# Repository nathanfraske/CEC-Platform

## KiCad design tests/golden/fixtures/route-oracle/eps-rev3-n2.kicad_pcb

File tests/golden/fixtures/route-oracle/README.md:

# route-oracle grader fixtures (SLICE-1a)

Two EPS-8pin PLACEMENTS (unrouted), used by `tests/test_route_oracle.py` to give the
route-oracle grader (`cec_synth_pipeline.route_oracle_grade`) durable PASS/FAIL teeth +
the proxy-vs-oracle disagreement case.

- `eps-rev3-n2.kicad_pcb` — the FIRST gate-clean EPS placement (commit 515cae7): the INA238
  current-sense ICs backed off the shunt 1.4 mm so the §6.8 inner-edge Kelvin tap clears the
  IC's own GND/+3V3 pads. Routes GATE-CLEAN under the recipe (kelvin_ok, foreign 0/0, drc 0,
  thermal ~62 C). The grader must rank it PASS.
- `eps-rev3-widegap-m.kicad_pcb` — its PRE-FIX parent (INA seated hard against the shunt).
  PROXY-BETTER (slightly lower HPWL, the tighter seat = shorter wires) but routes DIRTY
  (kelvin_ok=False: the LO->IN- tap strands). The grader must rank it FAIL. This is the
  concrete placement_proxy-vs-oracle DISAGREEMENT: the proxy prefers the tighter (broken)
  parent; the oracle, by actually routing, correctly demotes it.

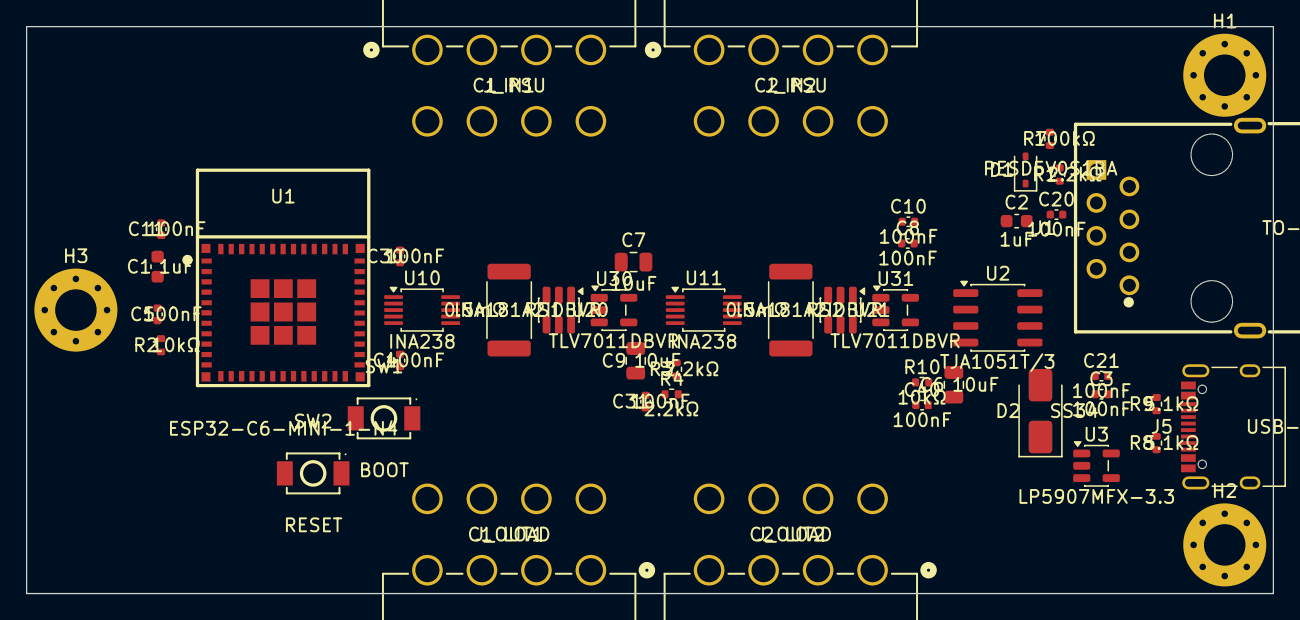
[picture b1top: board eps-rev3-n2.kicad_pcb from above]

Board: 4 copper layers, 96.1 x 43.7 mm, 48 parts (0 on the bottom side), 28 nets, no tracks yet.

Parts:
C1, C2: 1uF; C_0603_1608Metric
C3, C4, C5, C8, C10, C11, C20, C21, C30, C31, C40: 100nF; C_0402_1005Metric
C6, C7, C9: 10uF; C_0805_2012Metric
D1: PESD5V0S1BA; D_SOD-323
D2: SS34; D_SMA
H1, H2, H3: MountingHole_3.2mm_M3_Pad_Via
J1: TO-HUB; RJ45_FTP_Shielded_Horizontal
J5: USB-C 2.0; USB_C_Receptacle_XKB_U262-16XN-4BVC11
J_IN1: C1 PSU; Molex_Mini-Fit_Jr_87427-0802_2x04_P4.20mm_RA
J_IN2: C2 PSU; Molex_Mini-Fit_Jr_87427-0802_2x04_P4.20mm_RA
J_OUT1: C1 LOAD; Molex_Mini-Fit_Jr_87427-0802_2x04_P4.20mm_RA
J_OUT2: C2 LOAD; Molex_Mini-Fit_Jr_87427-0802_2x04_P4.20mm_RA
R1, R3, R4: 2.2kΩ; R_0402_1005Metric
R2, R10: 10kΩ; R_0402_1005Metric
R7: 100kΩ; R_0402_1005Metric
R8, R9: 5.1kΩ; R_0402_1005Metric
RS1, RS2: 0.5mΩ; R_2512_6332Metric
SW1: BOOT; TS-1088-AR02016
SW2: RESET; TS-1088-AR02016
U1: ESP32-C6-MINI-1-N4; ESP32-C6-MINI-1
U2: TJA1051T/3; SOIC-8_3.9x4.9mm_P1.27mm
U3: LP5907MFX-3.3; SOT-23-5
U10, U11: INA238; VSSOP-10_3x3mm_P0.5mm
U20, U21: INA181A2IDBVR; SOT-23-6
U30, U31: TLV7011DBVR; SOT-23-5

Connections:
+3V3: C2.1, C3.1, C7.1, C8.1, C10.1, C11.1, C20.1, C21.1, C30.1, C31.1, R2.1, R3.2, R4.2, U1.3, U2.5, U3.5, U10.6, U11.2, U11.6, U20.6, U21.6, U30.5, U31.5
+5VSB: C1.1, C4.1, C6.1, D2.1, J1.1, U2.3, U3.1, U3.3
/CAN_H: J1.3, U2.7
/CAN_L: J1.6, U2.6
/CAN_RX: U1.27, U2.4
/CAN_TX: U1.26, U2.1
/DETAMPC1: U20.1, U30.3
/DETAMPC2: U21.1, U31.3
/DETC1: U1.28, U30.1
/DETC2: U1.29, U31.1
/DETECT: D1.1, J1.8, R1.1, R7.1
/DETECT_SENSE: R7.2, U1.12
/EN: C5.1, R2.2, SW2.2, U1.8
/GPIO0: SW1.2, U1.23
/I2C_SCL: R4.1, U1.25, U10.5, U11.5
/I2C_SDA: R3.1, U1.24, U10.4, U11.4
/SENSEC1_HI: J_IN1.5, J_IN1.6, J_IN1.7, J_IN1.8, RS1.1, U10.10, U20.3
/SENSEC1_LO: J_OUT1.5, J_OUT1.6, J_OUT1.7, J_OUT1.8, RS1.2, U10.8, U10.9, U20.4
/SENSEC2_HI: J_IN2.5, J_IN2.6, J_IN2.7, J_IN2.8, RS2.1, U11.10, U21.3
/SENSEC2_LO: J_OUT2.5, J_OUT2.6, J_OUT2.7, J_OUT2.8, RS2.2, U11.8, U11.9, U21.4
/THRESH: C40.1, R10.2, U30.4, U31.4
/THRESH_PWM: R10.1, U1.19
/USB_CC1: J5.A5, R8.1
/USB_CC2: J5.B5, R9.1
/USB_D_N: J5.A7, J5.B7, U1.17
/USB_D_P: J5.A6, J5.B6, U1.18
/VBUS: C9.1, D2.2, J5.A4, J5.A9, J5.B4, J5.B9
GND: C1.2, C2.2, C3.2, C4.2, C5.2, C6.2, C7.2, C8.2, C9.2, C10.2, C11.2, C20.2, C21.2, C30.2, C31.2, C40.2, D1.2, H1.1, H2.1, H3.1, J1.2, J1.SH1, J1.SH2, J5.A1, J5.A12, J5.B1, J5.B12, J5.S1, J_IN1.1, J_IN1.2, J_IN1.3, J_IN1.4, J_IN2.1, J_IN2.2, J_IN2.3, J_IN2.4, J_OUT1.1, J_OUT1.2, J_OUT1.3, J_OUT1.4, J_OUT2.1, J_OUT2.2, J_OUT2.3, J_OUT2.4, R1.2, R8.2, R9.2, SW1.1, SW2.1, U1.1, U1.2, U1.11, U1.14, U1.36, U1.37, U1.38, U1.39, U1.40, U1.41, U1.42, U1.43, U1.44, U1.45, U1.46, U1.47, U1.48, U1.49, U1.50, U1.51, U1.52, U1.53, U2.2, U2.8, U3.2, U10.1, U10.2, U10.7, U11.1, U11.7, U20.2, U20.5, U21.2, U21.5, U30.2, U31.2
